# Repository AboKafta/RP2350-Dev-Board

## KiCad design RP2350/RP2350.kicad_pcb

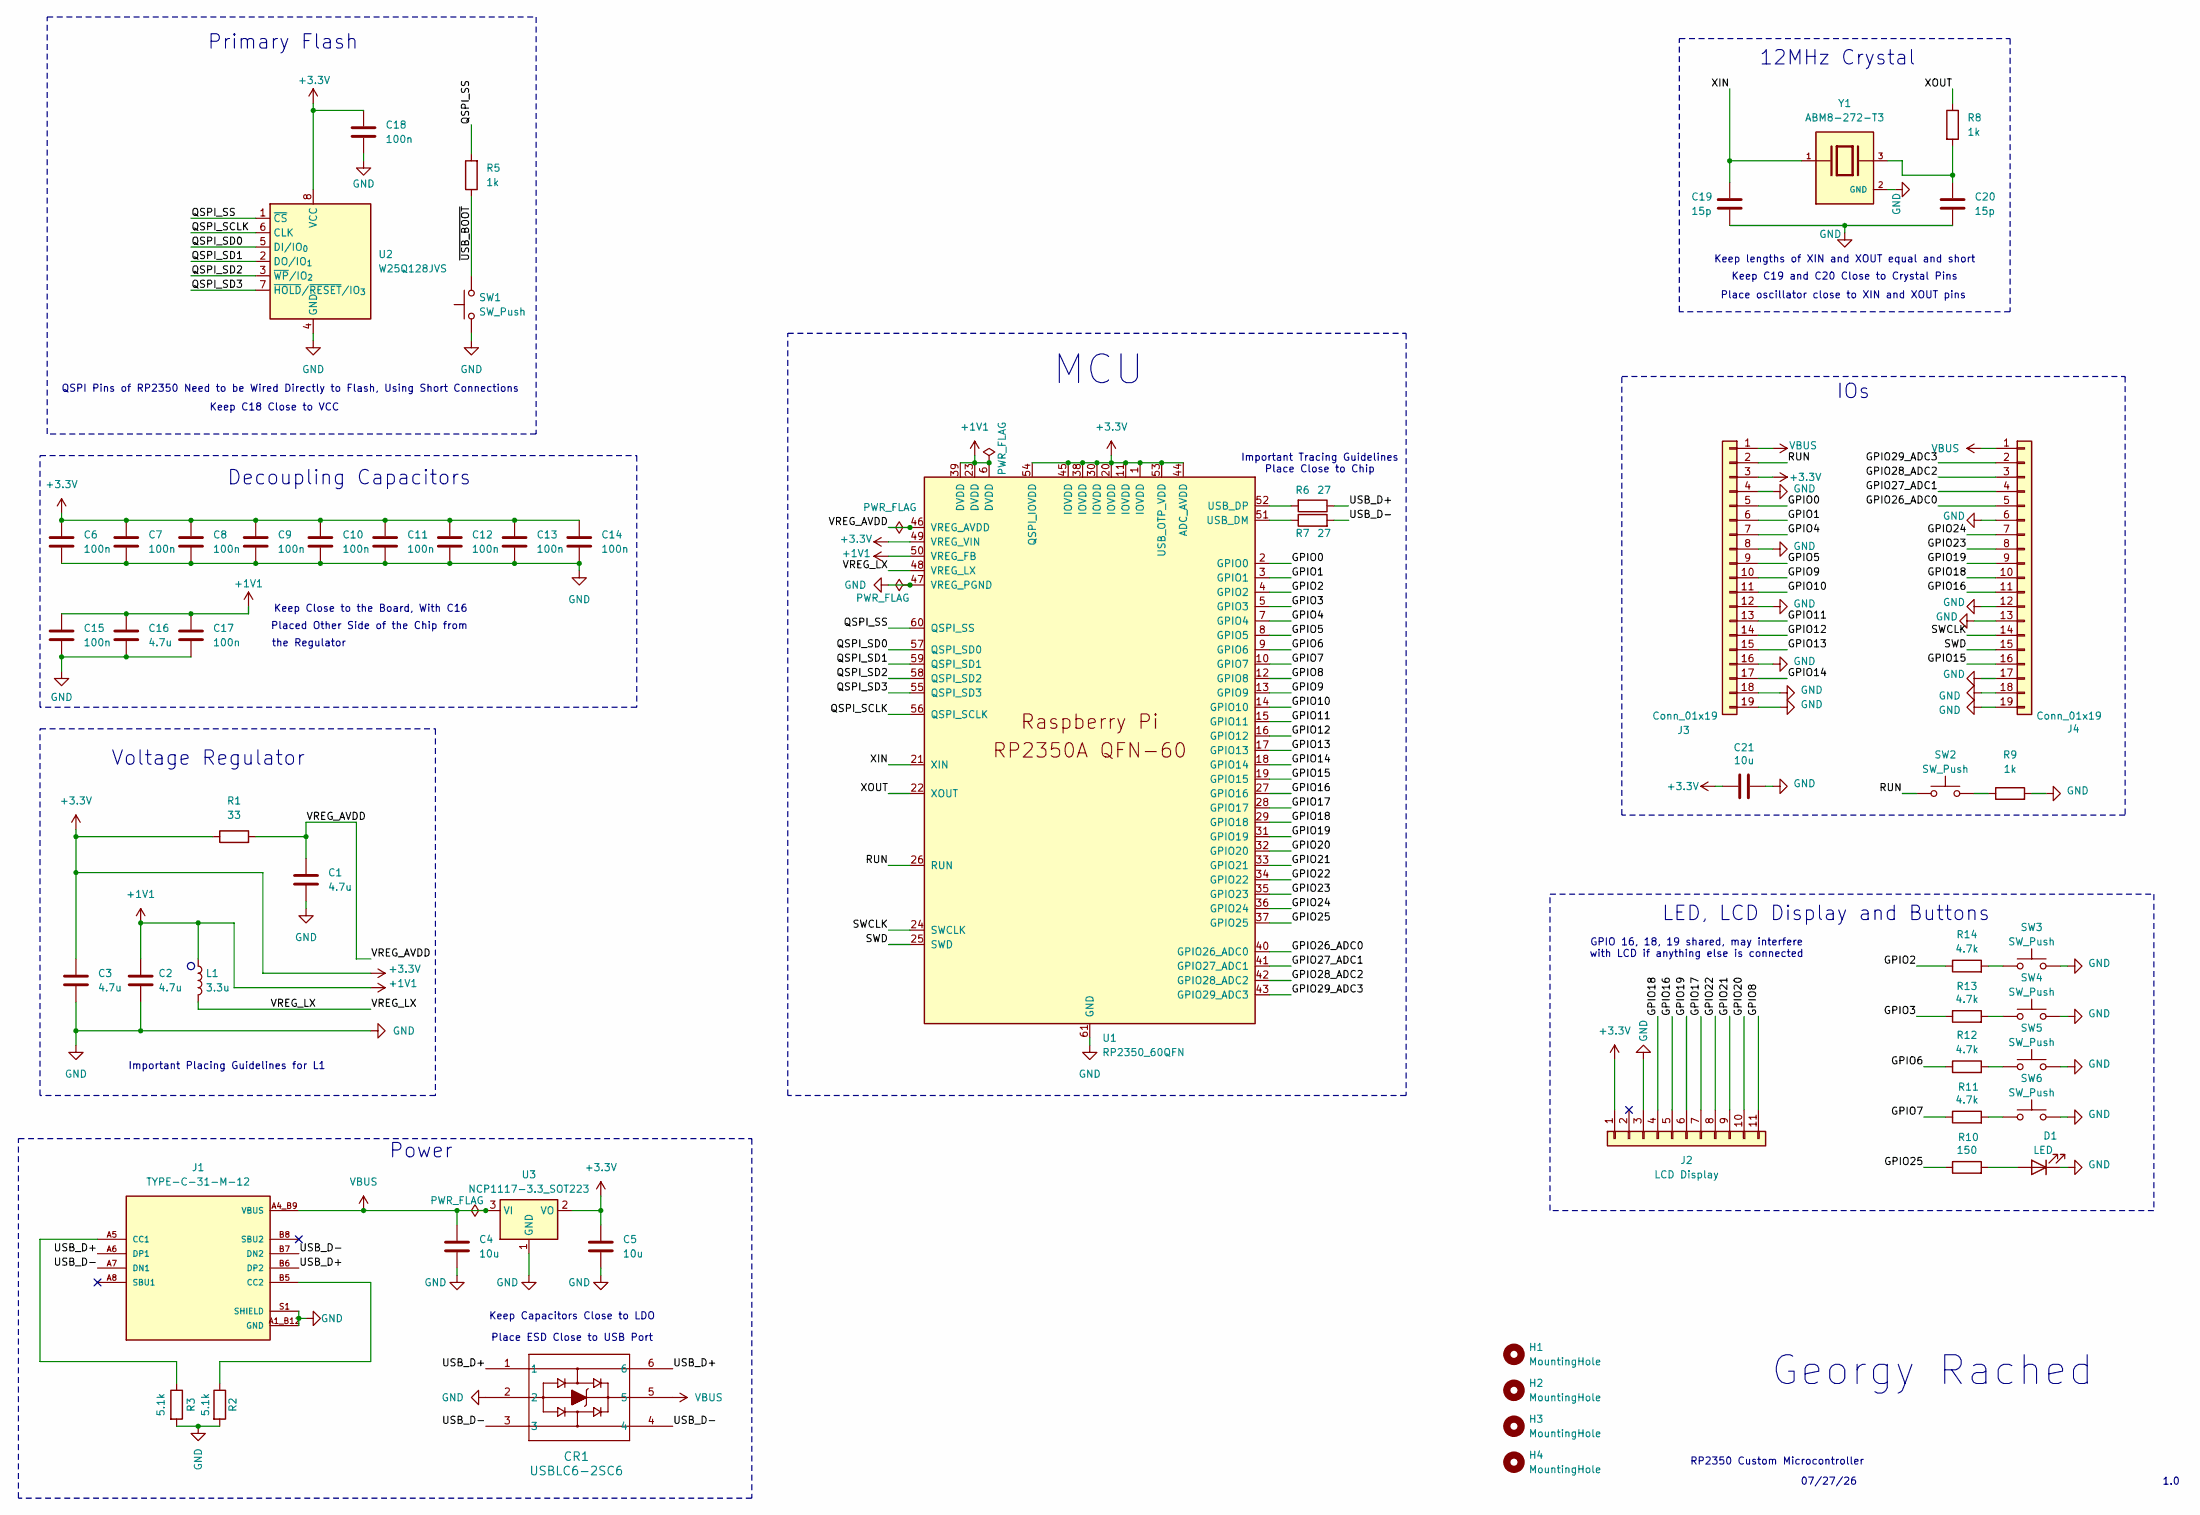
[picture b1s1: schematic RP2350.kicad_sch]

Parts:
C1, C2, C3, C16: 4.7u; C_0402_1005Metric
C4, C5, C21: 10u; C_0805_2012Metric
C6, C7, C8, C9, C10, C11, C12, C13, C14, C15, C17, C18: 100n; C_0402_1005Metric
C19, C20: 15p; C_0402_1005Metric
CR1: USBLC6-2SC6; SOT23-6L_STM
D1: LED; LED_0805_2012Metric
H1, H2, H3, H4: MountingHole; MountingHole_2.5mm
J1: TYPE-C-31-M-12; HRO_TYPE-C-31-M-12; PARTREV 2020.12.08
J2: LCD Display; 3533 1x11
J3, J4: Conn_01x19; PinHeader_1x19_P2.54mm_Vertical
L1: 3.3u; L_pol_2016
R1: 33; R_0402_1005Metric
R2, R3: 5.1k; R_0402_1005Metric
R5, R8, R9: 1k; R_0402_1005Metric
R6, R7: 27; R_0402_1005Metric
R10: 150; R_0402_1005Metric
R11, R12, R13, R14: 4.7k; R_0402_1005Metric
SW1, SW2, SW3, SW4, SW5, SW6: SW_Push; SW_PUSH_6mm_H4.3mm
U1: RP2350_60QFN; RP2350-QFN-60-1EP_7x7_P0.4mm_EP3.4x3.4mm_ThermalVias
U2: W25Q128JVS; SOIC-8_5.3x5.3mm_P1.27mm
U3: NCP1117-3.3_SOT223; SOT-223-3_TabPin2
Y1: ABM8-272-T3; XTAL_ABM8-272-T3; PARTREV 07-29-20

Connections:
+1V1: C2.1, C15.1, C16.1, C17.1, L1.1, U1.6 (DVDD), U1.23 (DVDD), U1.39 (DVDD), U1.50 (VREG_FB)
+3.3V: C3.1, C5.1, C6.1, C7.1, C8.1, C9.1, C10.1, C11.1, C12.1, C13.1, C14.1, C18.1, C21.1, J2.1 (VIN), J3.3, R1.1, U1.1 (IOVDD), U1.11 (IOVDD), U1.20 (IOVDD), U1.30 (IOVDD), U1.38 (IOVDD), U1.44 (ADC_AVDD), U1.45 (IOVDD), U1.49 (VREG_VIN), U1.53 (USB_OTP_VDD), U1.54 (QSPI_IOVDD), U2.8 (VCC), U3.2 (VO)
/GPIO0: J3.5, U1.2 (GPIO0)
/GPIO1: J3.6, U1.3 (GPIO1)
/GPIO2: R14.1, U1.4 (GPIO2)
/GPIO3: R13.1, U1.5 (GPIO3)
/GPIO4: J3.7, U1.7 (GPIO4)
/GPIO5: J3.9, U1.8 (GPIO5)
/GPIO6: R12.1, U1.9 (GPIO6)
/GPIO7: R11.1, U1.10 (GPIO7)
/GPIO8: J2.11 (LIT), U1.12 (GPIO8)
/GPIO9: J3.10, U1.13 (GPIO9)
/GPIO10: J3.11, U1.14 (GPIO10)
/GPIO11: J3.13, U1.15 (GPIO11)
/GPIO12: J3.14, U1.16 (GPIO12)
/GPIO13: J3.15, U1.17 (GPIO13)
/GPIO14: J3.17, U1.18 (GPIO14)
/GPIO15: J4.16, U1.19 (GPIO15)
/GPIO16: J2.5 (MISO), J4.11, U1.27 (GPIO16)
/GPIO17: J2.7 (TFTCS), U1.28 (GPIO17)
/GPIO18: J2.4 (SCK), J4.10, U1.29 (GPIO18)
/GPIO19: J2.6 (MOSI), J4.9, U1.31 (GPIO19)
/GPIO20: J2.10 (SDCS), U1.32 (GPIO20)
/GPIO21: J2.9 (DC), U1.33 (GPIO21)
/GPIO22: J2.8 (RST), U1.34 (GPIO22)
/GPIO23: J4.8, U1.35 (GPIO23)
/GPIO24: J4.7, U1.36 (GPIO24)
/GPIO25: R10.1, U1.37 (GPIO25)
/GPIO26_ADC0: J4.5, U1.40 (GPIO26_ADC0)
/GPIO27_ADC1: J4.4, U1.41 (GPIO27_ADC1)
/GPIO28_ADC2: J4.3, U1.42 (GPIO28_ADC2)
/GPIO29_ADC3: J4.2, U1.43 (GPIO29_ADC3)
/QSPI_SCLK: U1.56 (QSPI_SCLK), U2.6 (CLK)
/QSPI_SD0: U1.57 (QSPI_SD0), U2.5 (DI/IO_{0})
/QSPI_SD1: U1.59 (QSPI_SD1), U2.2 (DO/IO_{1})
/QSPI_SD2: U1.58 (QSPI_SD2), U2.3 (~WP/IO_{2})
/QSPI_SD3: U1.55 (QSPI_SD3), U2.7 (~HOLD/~RESET/IO_{3})
/QSPI_SS: R5.2, U1.60 (QSPI_SS), U2.1 (~CS)
/RUN: J3.2, SW2.1, U1.26 (RUN)
/SWCLK: J4.14, U1.24 (SWCLK)
/SWD: J4.15, U1.25 (SWD)
/USB_D+: CR1.1, CR1.6, J1.A6 (DP1), J1.B6 (DP2), R6.1
/USB_D-: CR1.3, CR1.4, J1.A7 (DN1), J1.B7 (DN2), R7.2
/VREG_AVDD: C1.1, R1.2, U1.46 (VREG_AVDD)
/VREG_LX: L1.2, U1.48 (VREG_LX)
/XIN: C19.1, U1.21 (XIN), Y1.1
/XOUT: R8.1, U1.22 (XOUT)
/~USB_BOOT: R5.1, SW1.2
GND: C1.2, C2.2, C3.2, C4.2, C5.2, C6.2, C7.2, C8.2, C9.2, C10.2, C11.2, C12.2, C13.2, C14.2, C15.2, C16.2, C17.2, C18.2, C19.2, C20.2, C21.2, CR1.2, D1.1 (K), J1.A1_B12 (GND), J1.B1_A12 (GND), J1.S1 (SHIELD), J1.S2 (SHIELD), J1.S3 (SHIELD), J1.S4 (SHIELD), J2.3 (GND), J3.4, J3.8, J3.12, J3.16, J3.18, J3.19, J4.6, J4.12, J4.13, J4.17, J4.18, J4.19, R2.2, R3.2, R9.2, SW1.1, SW3.2, SW4.2, SW5.2, SW6.2, U1.47 (VREG_PGND), U1.61 (GND), U2.4 (GND), U3.1 (GND), Y1.2 (GND), Y1.4 (GND)
unnamed: C20.1, R8.2, Y1.3
unnamed: D1.2 (A), R10.2
unnamed: J1.A5 (CC1), R3.1
unnamed: J1.B5 (CC2), R2.1
unnamed: R9.1, SW2.2
unnamed: R11.2, SW6.1
unnamed: R12.2, SW5.1
unnamed: R13.2, SW4.1
unnamed: R14.2, SW3.1
unnamed: R7.1, U1.51 (USB_DM)
unnamed: R6.2, U1.52 (USB_DP)
VBUS: C4.1, CR1.5, J1.A4_B9 (VBUS), J1.B4_A9 (VBUS), J3.1, J4.1, U3.3 (VI)

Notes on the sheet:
Keep C19 and C20 Close to Crystal Pins
Power
Keep lengths of XIN and XOUT equal and short
QSPI Pins of RP2350 Need to be Wired Directly to Flash, Using Short Connections
Keep Capacitors Close to LDO
Important Placing Guidelines for L1
the Regulator
GPIO 16, 18, 19 shared, may interfere with LCD if anything else is connected
Place ESD Close to USB Port
Primary Flash
Decoupling Capacitors
Voltage Regulator
Place oscillator close to XIN and XOUT pins
12MHz Crystal
IOs
Important Tracing Guidelines Place Close to Chip
Keep C18 Close to VCC
07/27/26
LED, LCD Display and Buttons
1.0
Georgy Rached
Keep Close to the Board, With C16
Placed Other Side of the Chip from
MCU
RP2350 Custom Microcontroller

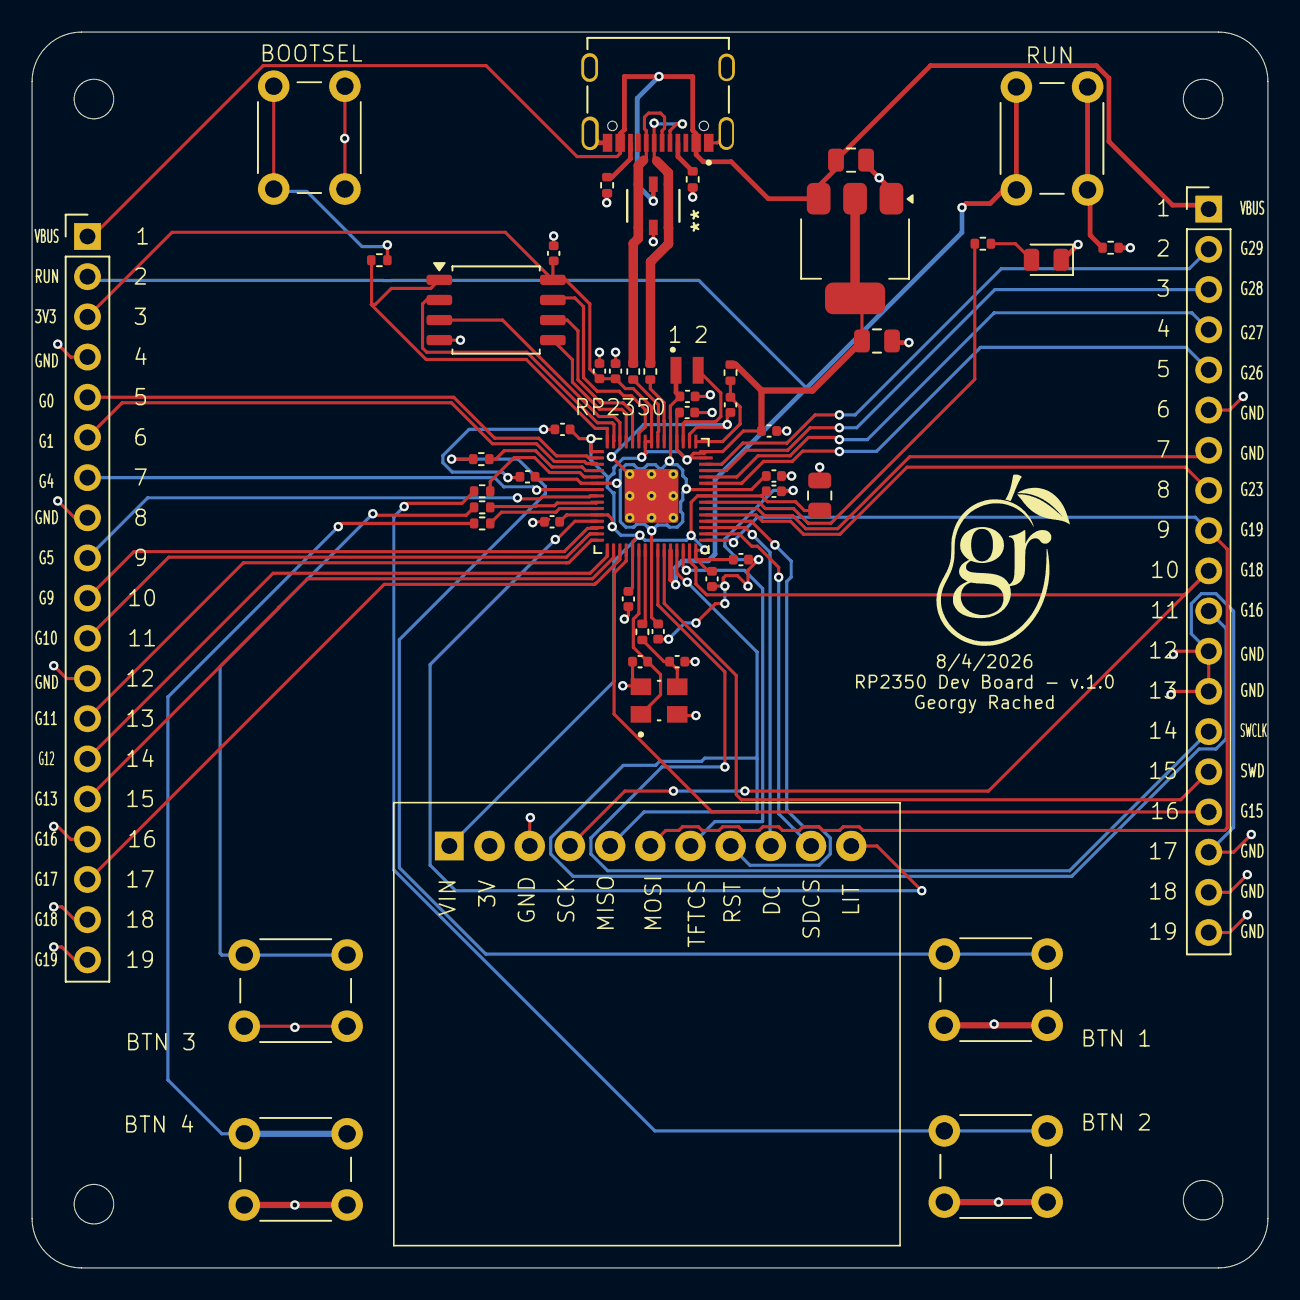
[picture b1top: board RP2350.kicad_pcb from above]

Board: 4 copper layers, 78.1 x 78.1 mm, 55 parts (0 on the bottom side), 61 nets.
